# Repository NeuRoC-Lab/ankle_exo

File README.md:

# ankle_exo
This repository stores the algorithms to operate The OpenExo Styled exoskeleton.

# instructions 

To run the Arduino-Teensy CAN sender receiver test do : 

(1) Connect each of the Arduino R4 and run `pio run -e can_module_arduinos_receiver` or `pio run -e can_module_arduinos_sender` for the receiver arduino and the sender arduino respectively 

(2) Connect one Teensy, run `pio run -e can_module_teensy_receiver` / `pio run -e can_module_teensy_sender` then do same as (1) for the remaining Arduino 

## CubeMars connection with the SN65HVD230 CAN Transceiver module + Arduino Uno R4

Run the Arduino code with `pio run -e arduino_can_cubemars` which will move the motor back and forth 

# A web documentation is available at [this website](https://oscartesniere.com/ankledocs/).

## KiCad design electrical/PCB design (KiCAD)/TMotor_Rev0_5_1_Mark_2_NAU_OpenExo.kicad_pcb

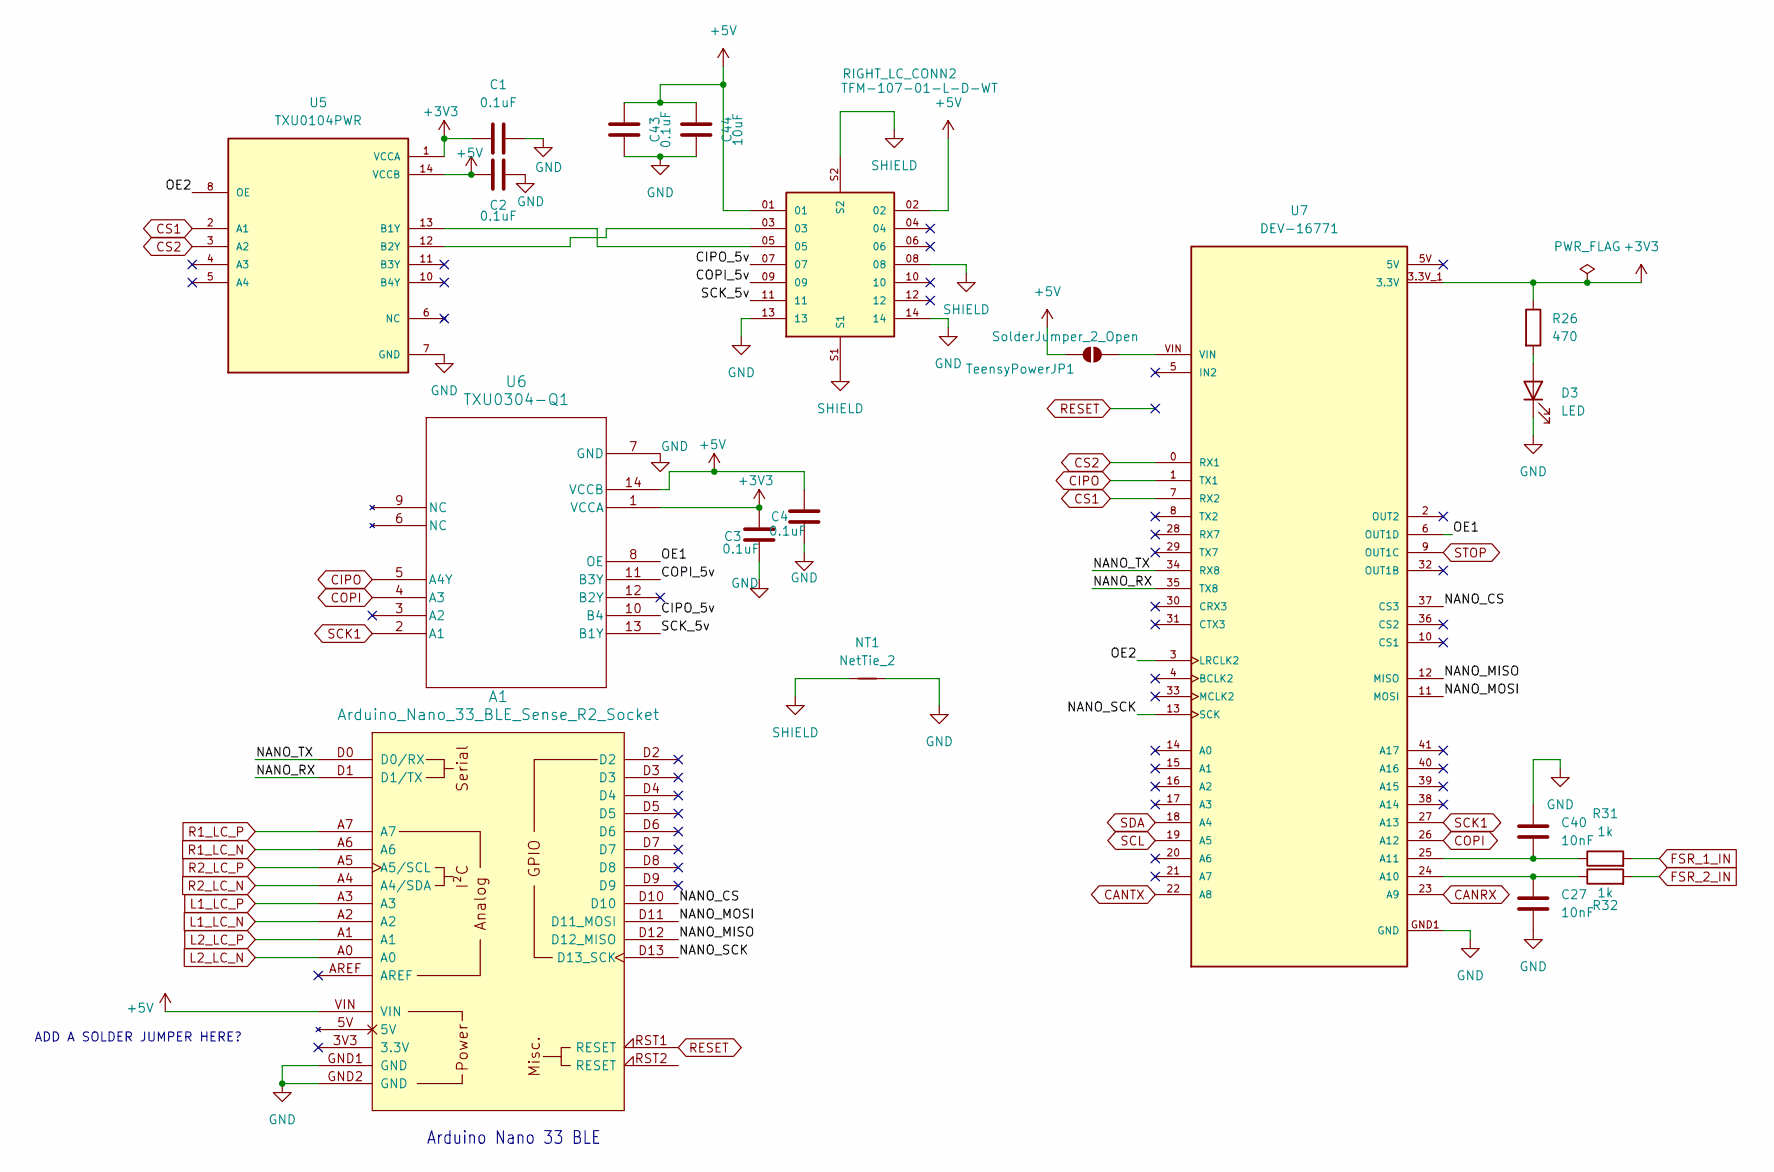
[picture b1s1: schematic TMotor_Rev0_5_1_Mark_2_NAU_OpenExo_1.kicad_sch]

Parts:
A1: Arduino_Nano_33_BLE_Sense_R2_Socket; Arduino_Nano_Every_Socket
C1, C2, C3, C4, C43: 0.1uF; C_0805_2012Metric_Pad1.18x1.45mm_HandSolder
C27, C40: 10nF; C_0805_2012Metric_Pad1.18x1.45mm_HandSolder
C44: 10uF; C_0805_2012Metric_Pad1.18x1.45mm_HandSolder
D3: LED; LED_0805_2012Metric
NT1: NetTie_2; NetTie-2_SMD_Pad0.5mm
R26: 470; R_0805_2012Metric_Pad1.20x1.40mm_HandSolder
R31, R32: 1k; R_0805_2012Metric_Pad1.20x1.40mm_HandSolder
RIGHT_LC_CONN2: TFM-107-01-L-D-WT; SAMTEC_TFM-107-01-L-D-WT; PARTREV T
TeensyPowerJP1: SolderJumper_2_Open; SolderJumper-2_P1.3mm_Open_RoundedPad1.0x1.5mm
U5: TXU0104PWR; SOIC_QPWRQ1_TEX; PARTREV A
U6: TXU0304-Q1; PW14_TXU0304-Q1_TEX
U7: DEV-16771; MODULE_DEV-16771; PARTREV 4.1

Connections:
+3V3: C1.1, C3.2, R26.1, U5.1 (VCCA), U6.1 (VCCA), U7.3.3V_1 (3.3V), U7.3.3V_2 (3.3V), U7.3.3V_3 (3.3V); also elsewhere on the board
/MCUs/CIPO_5v: RIGHT_LC_CONN2.07, U6.10 (B4)
/MCUs/COPI_5v: RIGHT_LC_CONN2.09, U6.11 (B3Y)
/MCUs/NANO_CS: A1.D10, U7.37 (CS3)
/MCUs/NANO_MISO: A1.D12 (D12_MISO), U7.12 (MISO)
/MCUs/NANO_MOSI: A1.D11 (D11_MOSI), U7.11 (MOSI)
/MCUs/NANO_RX: A1.D1 (D1/TX), U7.35 (TX8)
/MCUs/NANO_SCK: A1.D13 (D13_SCK), U7.13 (SCK)
/MCUs/NANO_TX: A1.D0 (D0/RX), U7.34 (RX8)
/MCUs/OE1: U6.8 (OE), U7.6 (OUT1D)
/MCUs/OE2: U5.8 (OE), U7.3 (LRCLK2)
/MCUs/SCK_5v: RIGHT_LC_CONN2.11, U6.13 (B1Y)
CANRX: U7.23 (A9); also elsewhere on the board
CANTX: U7.22 (A8); also elsewhere on the board
CIPO: U6.5 (A4Y), U7.1 (TX1)
COPI: U6.4 (A3), U7.26 (A12)
CS1: U5.2 (A1), U7.7 (RX2)
CS2: U5.3 (A2), U7.0 (RX1)
FSR_1_IN: R31.2; also elsewhere on the board
FSR_2_IN: R32.2; also elsewhere on the board
GND: A1.GND1 (GND), A1.GND2 (GND), C1.2, C2.2, C3.1, C4.1, C27.2, C40.1, C43.1, C44.1, D3.1 (K), NT1.2, RIGHT_LC_CONN2.13, RIGHT_LC_CONN2.14, U5.7 (GND), U6.7 (GND), U7.GND1 (GND), U7.GND2 (GND), U7.GND3 (GND), U7.GND4 (GND), U7.GND5 (GND); also elsewhere on the board
L1_LC_N: A1.A2; also elsewhere on the board
L1_LC_P: A1.A3; also elsewhere on the board
L2_LC_N: A1.A0; also elsewhere on the board
L2_LC_P: A1.A1; also elsewhere on the board
unnamed: D3.2 (A), R26.2
unnamed: TeensyPowerJP1.1 (A), U7.VIN
unnamed: RIGHT_LC_CONN2.05, U5.13 (B1Y)
unnamed: RIGHT_LC_CONN2.03, U5.12 (B2Y)
unnamed: C27.1, R32.1, U7.24 (A10)
unnamed: C40.2, R31.1, U7.25 (A11)
R1_LC_N: A1.A6; also elsewhere on the board
R1_LC_P: A1.A7; also elsewhere on the board
R2_LC_N: A1.A4 (A4/SDA); also elsewhere on the board
R2_LC_P: A1.A5 (A5/SCL); also elsewhere on the board
RESET: A1.RST1 (RESET); also elsewhere on the board
SCK1: U6.2 (A1), U7.27 (A13)
SCL: U7.19 (A5); also elsewhere on the board
SDA: U7.18 (A4); also elsewhere on the board
SHIELD: NT1.1, RIGHT_LC_CONN2.08, RIGHT_LC_CONN2.S1, RIGHT_LC_CONN2.S2; also elsewhere on the board
STOP: U7.9 (OUT1C); also elsewhere on the board

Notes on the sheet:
ADD A SOLDER JUMPER HERE?
Arduino Nano 33 BLE

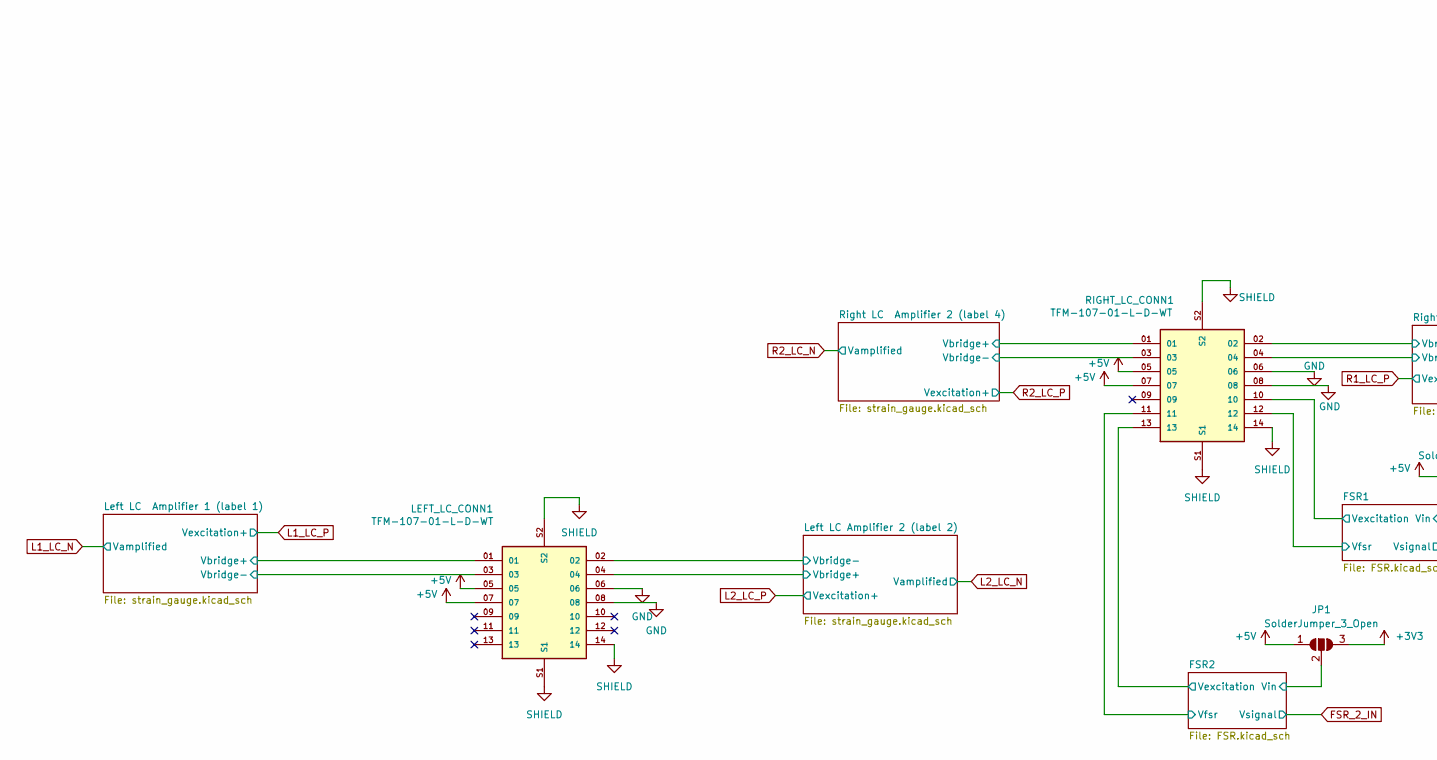
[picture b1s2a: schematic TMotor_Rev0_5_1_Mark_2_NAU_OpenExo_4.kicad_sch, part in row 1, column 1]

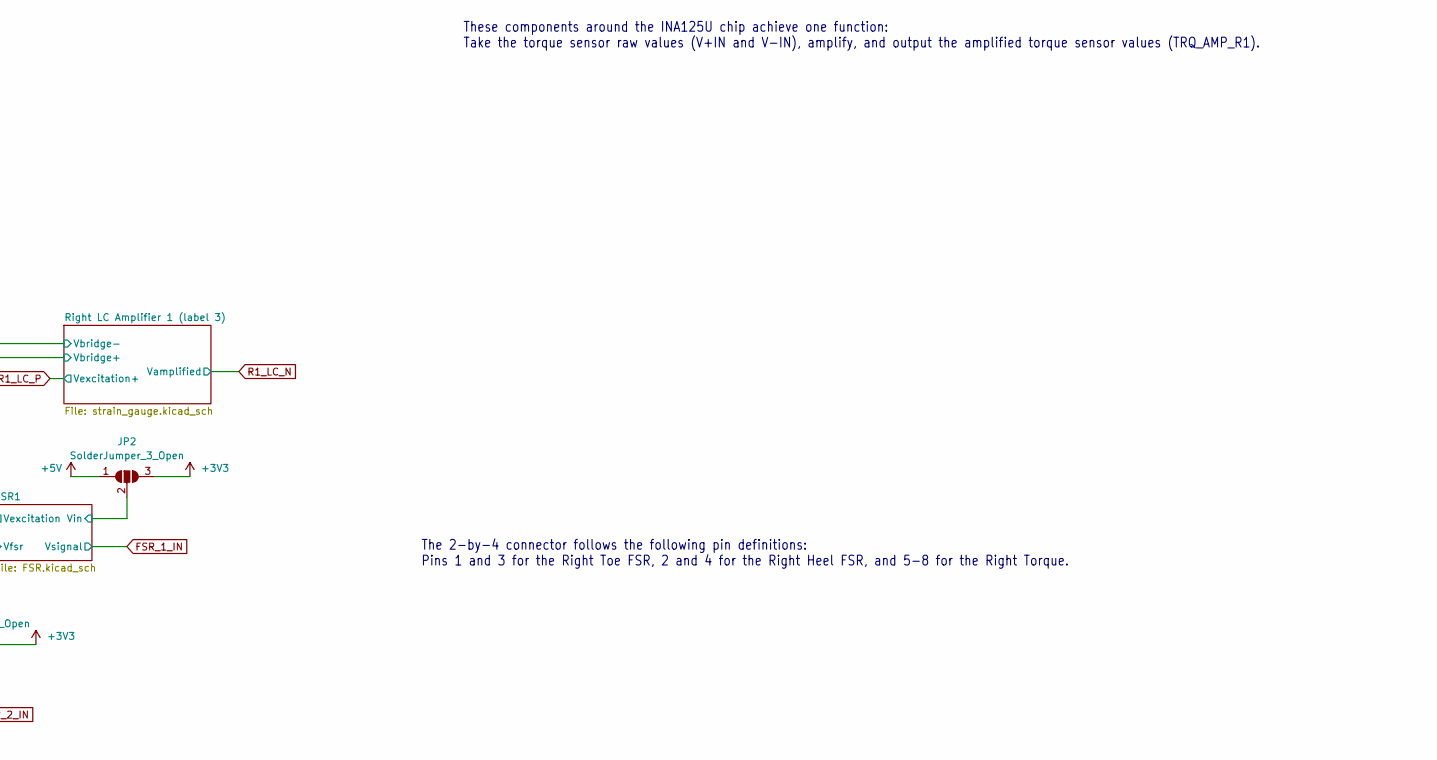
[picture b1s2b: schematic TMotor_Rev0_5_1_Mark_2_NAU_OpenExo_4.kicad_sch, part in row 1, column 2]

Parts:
JP1, JP2: SolderJumper_3_Open; SolderJumper-3_P1.3mm_Open_RoundedPad1.0x1.5mm
LEFT_LC_CONN1: TFM-107-01-L-D-WT; SAMTEC_TFM-107-01-L-D-WT; PARTREV T
RIGHT_LC_CONN1: TFM-107-01-L-D-WT; SAMTEC_TFM-107-01-L-D-WT; PARTREV T

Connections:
+3V3: JP1.3 (B), JP2.3 (B); also elsewhere on the board
/Load cells/FSR1/Vexcitation: JP2.2 (C), RIGHT_LC_CONN1.10
/Load cells/FSR2/Vexcitation: JP1.2 (C), RIGHT_LC_CONN1.13
/Load cells/Left LC Amplifier 1 (label 1)/Vbridge+: LEFT_LC_CONN1.01; also elsewhere on the board
/Load cells/Left LC Amplifier 1 (label 1)/Vbridge-: LEFT_LC_CONN1.03; also elsewhere on the board
/Load cells/Left LC Amplifier 2 (label 2)/Vbridge+: LEFT_LC_CONN1.04; also elsewhere on the board
/Load cells/Left LC Amplifier 2 (label 2)/Vbridge-: LEFT_LC_CONN1.02; also elsewhere on the board
/Load cells/Right LC Amplifier 2 (label 4)/Vbridge+: RIGHT_LC_CONN1.01; also elsewhere on the board
/Load cells/Right LC Amplifier 2 (label 4)/Vbridge-: RIGHT_LC_CONN1.03; also elsewhere on the board
/Load cells/Right LC Amplifier 1 (label 3)/Vbridge+: RIGHT_LC_CONN1.04; also elsewhere on the board
/Load cells/Right LC Amplifier 1 (label 3)/Vbridge-: RIGHT_LC_CONN1.02; also elsewhere on the board
FSR_1_IN: RIGHT_LC_CONN1.12; also elsewhere on the board
FSR_2_IN: RIGHT_LC_CONN1.11; also elsewhere on the board
GND: LEFT_LC_CONN1.06, LEFT_LC_CONN1.08, RIGHT_LC_CONN1.06, RIGHT_LC_CONN1.08; also elsewhere on the board
SHIELD: LEFT_LC_CONN1.14, LEFT_LC_CONN1.S1, LEFT_LC_CONN1.S2, RIGHT_LC_CONN1.14, RIGHT_LC_CONN1.S1, RIGHT_LC_CONN1.S2; also elsewhere on the board

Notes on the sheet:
The 2-by-4 connector follows the following pin definitions: Pins 1 and 3 for the Right Toe FSR, 2 and 4 for the Right Heel FSR, and 5-8 for the Right Torque.
These components around the INA125U chip achieve one function: Take the torque sensor raw values (V+IN and V-IN), amplify, and output the amplified torque sensor values (TRQ_AMP_R1).

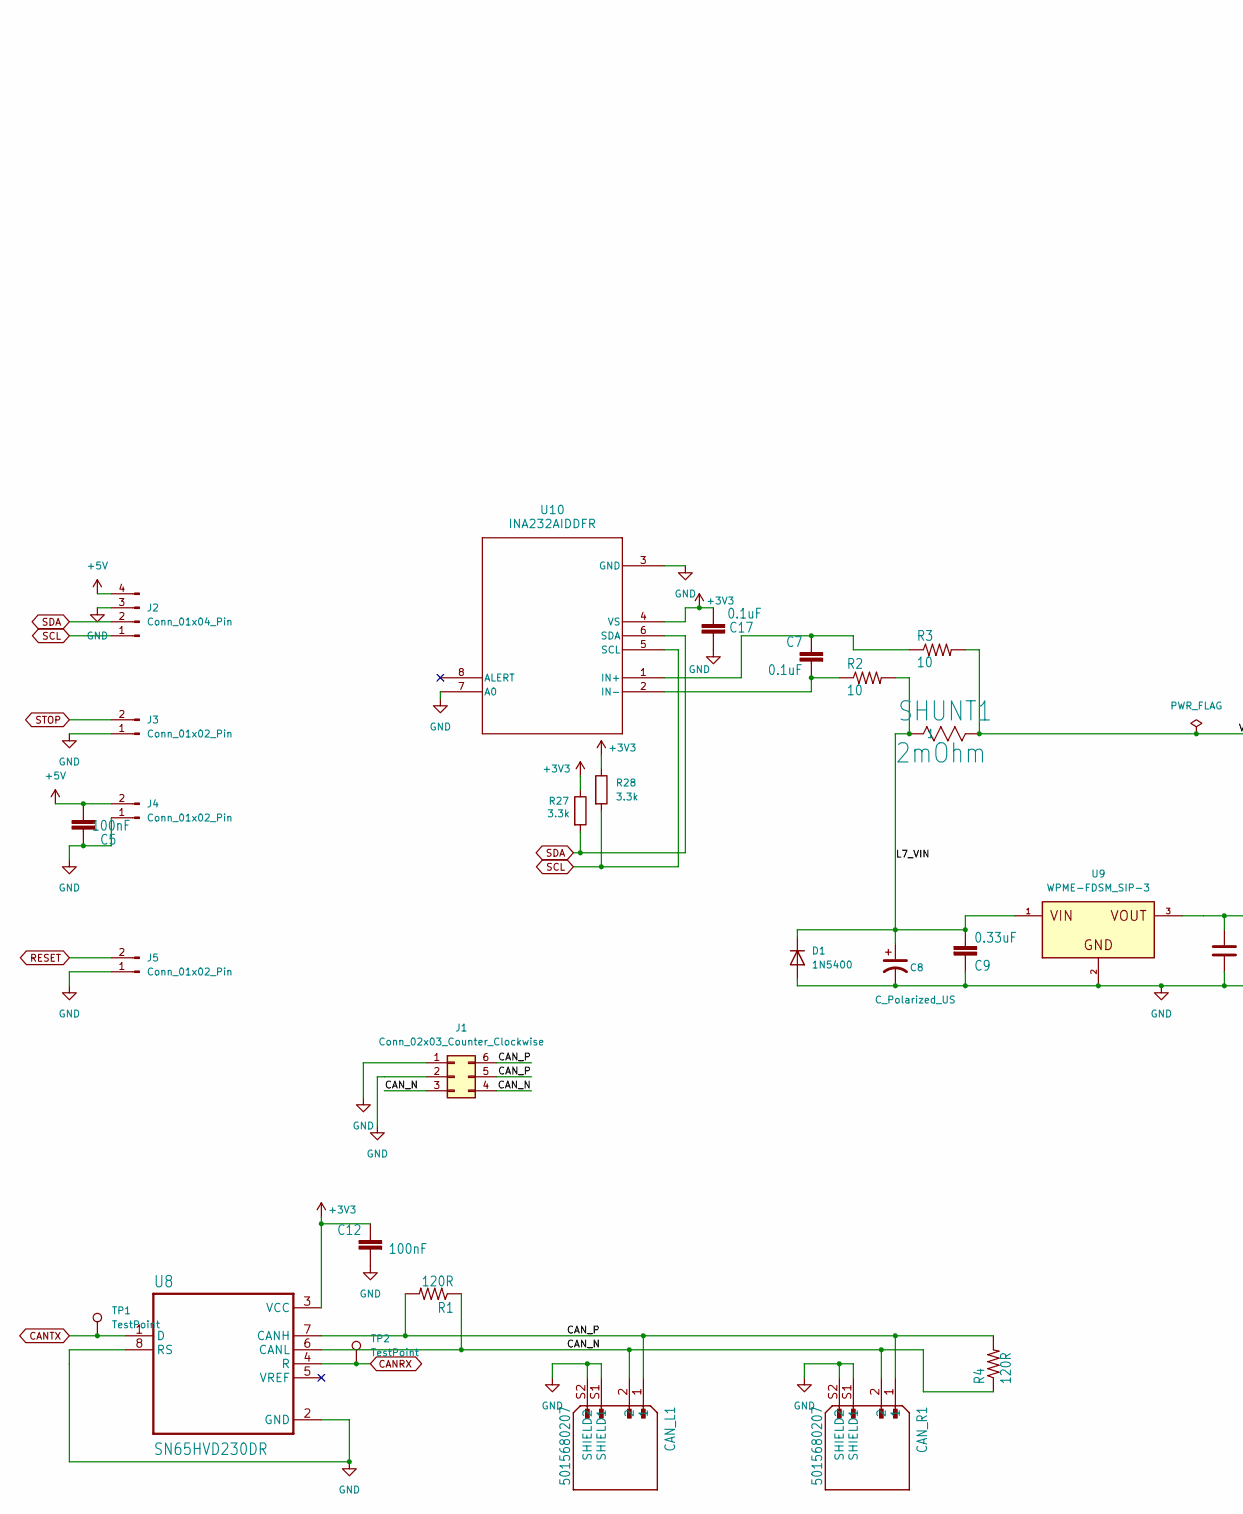
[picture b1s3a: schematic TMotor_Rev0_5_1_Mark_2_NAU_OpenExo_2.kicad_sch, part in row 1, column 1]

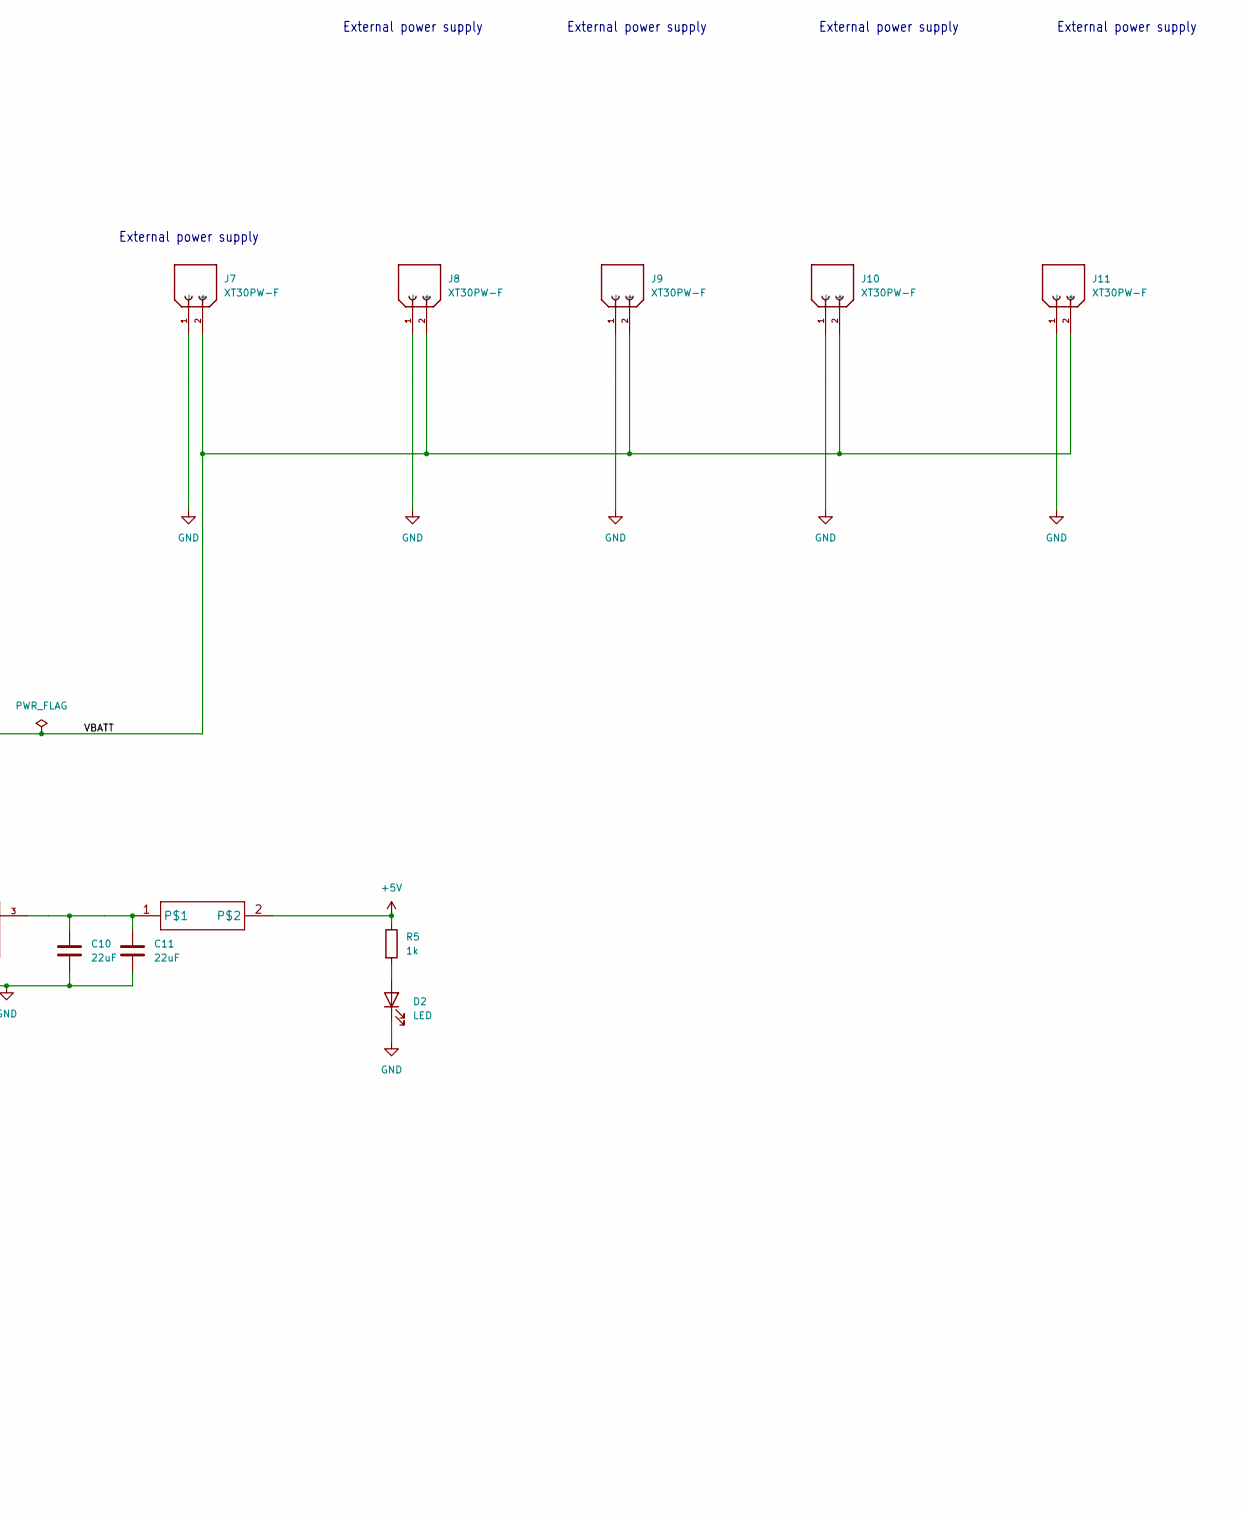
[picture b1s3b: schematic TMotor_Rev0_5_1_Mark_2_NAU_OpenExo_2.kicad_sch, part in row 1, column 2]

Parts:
C5, C12: 100nF; C_0805_2012Metric_Pad1.18x1.45mm_HandSolder
C7, C17: 0.1uF; C_0805_2012Metric_Pad1.18x1.45mm_HandSolder
C8: C_Polarized_US; CP_Radial_D10.0mm_P5.00mm
C9: 0.33uF; C_0805_2012Metric_Pad1.18x1.45mm_HandSolder
C10, C11: 22uF; C_0805_2012Metric_Pad1.18x1.45mm_HandSolder
CAN_L1: 5015680207; MOLEX_5015680207
CAN_R1: 5015680207; MOLEX_5015680207
D1: 1N5400; D_DO-201AD_P15.24mm_Horizontal
D2: LED; LED_0805_2012Metric
J1: Conn_02x03_Counter_Clockwise; PinHeader_2x03_P2.54mm_Vertical
J2: Conn_01x04_Pin; PinHeader_1x04_P2.54mm_Vertical
J3, J4, J5: Conn_01x02_Pin; PinHeader_1x02_P2.54mm_Vertical
J7, J8, J9, J10, J11: XT30PW-F; AMASS_XT30U-F_1x02_P5.0mm_Vertical; PARTREV 1.2
R1, R4: 120R; R_0805_2012Metric_Pad1.20x1.40mm_HandSolder
R2, R3: 10; R_0805_2012Metric_Pad1.20x1.40mm_HandSolder
R5: 1k; R_0805_2012Metric_Pad1.20x1.40mm_HandSolder
R27, R28: 3.3k; R_0805_2012Metric_Pad1.20x1.40mm_HandSolder
SHUNT1: 2mOhm; STA_CSNL2512(2)_STP
TP1, TP2: TestPoint; TestPoint_Keystone_5000-5004_Miniature
U8: SN65HVD230DR; SOIC127P599X175-8N
U9: WPME-FDSM_SIP-3; WPME-FDSM_17301XX35; DigiKey_Part_Number 732-173010535-ND
U10: INA232AIDDFR; SOT_32AIDDFR_TEX
U$1: 0458002.DR; FUSE_LITTEL_448

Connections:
+3V3: C12.1, C17.2, R27.1, R28.1, U8.3 (VCC), U10.4 (VS); also elsewhere on the board
/CAN and peripherals./CAN_N: CAN_L1.2, CAN_R1.2, J1.3, J1.4, R1.1, R4.1, U8.6 (CANL)
/CAN and peripherals./CAN_P: CAN_L1.1, CAN_R1.1, J1.5, J1.6, R1.2, R4.2, U8.7 (CANH)
/CAN and peripherals./L7_VIN: C8.1, C9.2, D1.1 (K), R2.2, SHUNT1.1, U9.1
/CAN and peripherals./VBATT: J7.2 (+), J8.2 (+), J9.2 (+), J10.2 (+), J11.2 (+), R3.2, SHUNT1.2
CANRX: TP2.1, U8.4 (R); also elsewhere on the board
CANTX: TP1.1, U8.1 (D); also elsewhere on the board
GND: C5.1, C8.2, C9.1, C10.2, C11.2, C12.2, C17.1, CAN_L1.S1 (SHIELD1), CAN_L1.S2 (SHIELD2), CAN_R1.S1 (SHIELD1), CAN_R1.S2 (SHIELD2), D1.2 (A), D2.1 (K), J1.1, J1.2, J2.3, J3.1, J4.1, J5.1, J7.1 (-), J8.1 (-), J9.1 (-), J10.1 (-), J11.1 (-), U8.2 (GND), U8.8 (RS), U9.2, U10.3 (GND), U10.7 (A0); also elsewhere on the board
unnamed: D2.2 (A), R5.2
unnamed: C7.1, R3.1, U10.1 (IN+)
unnamed: C7.2, R2.1, U10.2 (IN-)
unnamed: C10.1, C11.1, U9.3, U$1.1
RESET: J5.2; also elsewhere on the board
SCL: J2.1, R28.2, U10.5 (SCL); also elsewhere on the board
SDA: J2.2, R27.2, U10.6 (SDA); also elsewhere on the board
STOP: J3.2; also elsewhere on the board

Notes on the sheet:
External power supply

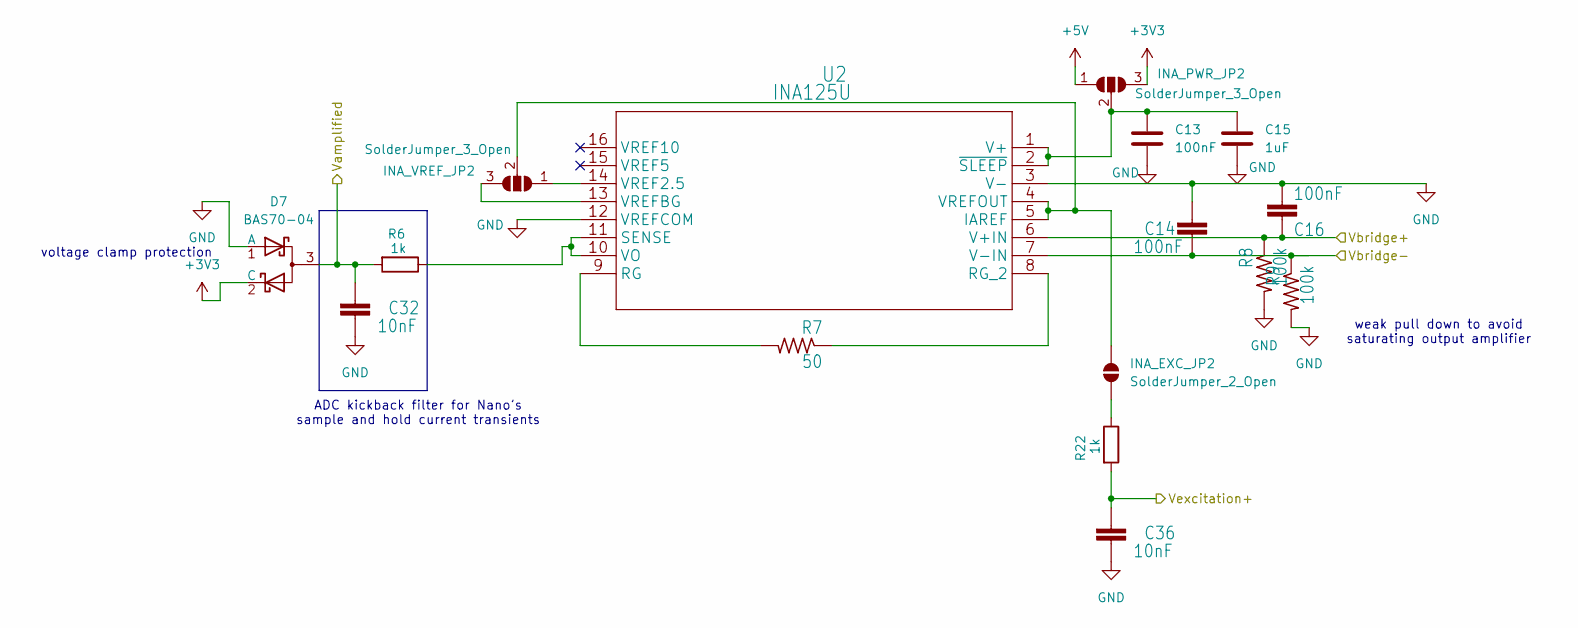
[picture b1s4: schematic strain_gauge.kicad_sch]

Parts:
C13, C14, C16: 100nF; C_0805_2012Metric_Pad1.18x1.45mm_HandSolder
C15: 1uF; C_0805_2012Metric_Pad1.18x1.45mm_HandSolder
C32, C36: 10nF; C_0805_2012Metric_Pad1.18x1.45mm_HandSolder
D7: BAS70-04; P200_SOT-23
INA_EXC_JP2: SolderJumper_2_Open; SolderJumper-2_P1.3mm_Open_RoundedPad1.0x1.5mm
INA_PWR_JP2: SolderJumper_3_Open; SolderJumper-3_P1.3mm_Open_RoundedPad1.0x1.5mm_NumberLabels
INA_VREF_JP2: SolderJumper_3_Open; SolderJumper-3_P1.3mm_Open_RoundedPad1.0x1.5mm_NumberLabels
R6, R22: 1k; R_0805_2012Metric_Pad1.20x1.40mm_HandSolder
R7: 50; R_0805_2012Metric_Pad1.20x1.40mm_HandSolder
R8, R9: 100k; R_0805_2012Metric_Pad1.20x1.40mm_HandSolder
U2: INA125U; D16

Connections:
+3V3: D7.2 (C), INA_PWR_JP2.3 (B); also elsewhere on the board
/Load cells/Left LC Amplifier 2 (label 2)/Vbridge+: C16.1, R8.1, U2.6 (V+IN); also elsewhere on the board
/Load cells/Left LC Amplifier 2 (label 2)/Vbridge-: C14.1, R9.1, U2.7 (V-IN); also elsewhere on the board
GND: C13.2, C14.2, C15.2, C16.2, C32.1, C36.1, D7.1 (A), R8.2, R9.2, U2.3 (V-), U2.12 (VREFCOM); also elsewhere on the board
L2_LC_N: C32.2, D7.3, R6.2; also elsewhere on the board
L2_LC_P: C36.2, R22.2; also elsewhere on the board
unnamed: INA_EXC_JP2.2 (B), R22.1
unnamed 48: INA_VREF_JP2.3 (B), U2.13 (VREFBG); also elsewhere on the board
unnamed: R7.2, U2.9 (RG)
unnamed: R7.1, U2.8 (RG_2)
unnamed: R6.1, U2.10 (VO), U2.11 (SENSE)

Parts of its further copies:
C18, C19, C21, C23, C24, C26, C28, C29, C31: 100nF; C_0805_2012Metric_Pad1.18x1.45mm_HandSolder
C20, C25, C30: 1uF; C_0805_2012Metric_Pad1.18x1.45mm_HandSolder
C33, C34, C35, C37, C38, C39: 10nF; C_0805_2012Metric_Pad1.18x1.45mm_HandSolder
D8, D9, D10: BAS70-04; P200_SOT-23
INA_EXC_JP1, INA_EXC_JP3, INA_EXC_JP4: SolderJumper_2_Open; SolderJumper-2_P1.3mm_Open_RoundedPad1.0x1.5mm
R10, R14, R18, R23, R24, R25: 1k; R_0805_2012Metric_Pad1.20x1.40mm_HandSolder
R11, R15, R19: 50; R_0805_2012Metric_Pad1.20x1.40mm_HandSolder
R12, R13, R16, R17, R20, R21: 100k; R_0805_2012Metric_Pad1.20x1.40mm_HandSolder
U1, U3, U4: INA125U; D16

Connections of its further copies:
+3V3: D8.2 (C), D9.2 (C), D10.2 (C); also elsewhere on the board
/Load cells/Left LC Amplifier 1 (label 1)/Vbridge+: C21.1, R12.1, U1.6 (V+IN); also elsewhere on the board
/Load cells/Left LC Amplifier 1 (label 1)/Vbridge-: C19.1, R13.1, U1.7 (V-IN); also elsewhere on the board
/Load cells/Right LC Amplifier 2 (label 4)/Vbridge+: C26.1, R16.1, U4.6 (V+IN); also elsewhere on the board
/Load cells/Right LC Amplifier 2 (label 4)/Vbridge-: C24.1, R17.1, U4.7 (V-IN); also elsewhere on the board
/Load cells/Right LC Amplifier 1 (label 3)/Vbridge+: C31.1, R20.1, U3.6 (V+IN); also elsewhere on the board
/Load cells/Right LC Amplifier 1 (label 3)/Vbridge-: C29.1, R21.1, U3.7 (V-IN); also elsewhere on the board
GND: C18.2, C19.2, C20.2, C21.2, C23.2, C24.2, C25.2, C26.2, C28.2, C29.2, C30.2, C31.2, C33.1, C34.1, C35.1, C37.1, C38.1, C39.1, D8.1 (A), D9.1 (A), D10.1 (A), R12.2, R13.2, R16.2, R17.2, R20.2, R21.2, U1.3 (V-), U1.12 (VREFCOM), U3.3 (V-), U3.12 (VREFCOM), U4.3 (V-), U4.12 (VREFCOM); also elsewhere on the board
L1_LC_N: C33.2, D8.3, R10.2; also elsewhere on the board
L1_LC_P: C37.2, R23.2; also elsewhere on the board
unnamed: INA_EXC_JP1.1 (A), U1.4 (VREFOUT), U1.5 (IAREF), U1.14 (VREF2.5)
unnamed: INA_EXC_JP1.2 (B), R23.1
unnamed: INA_EXC_JP3.1 (A), U3.4 (VREFOUT), U3.5 (IAREF), U3.14 (VREF2.5)
unnamed: INA_EXC_JP3.2 (B), R25.1
unnamed: INA_EXC_JP4.1 (A), U4.4 (VREFOUT), U4.5 (IAREF), U4.14 (VREF2.5)
unnamed: INA_EXC_JP4.2 (B), R24.1
unnamed 48: U1.13 (VREFBG), U3.13 (VREFBG), U4.13 (VREFBG); also elsewhere on the board
unnamed: R11.2, U1.9 (RG)
unnamed: R11.1, U1.8 (RG_2)
unnamed: R10.1, U1.10 (VO), U1.11 (SENSE)
unnamed: R19.2, U3.9 (RG)
unnamed: R19.1, U3.8 (RG_2)
unnamed: R18.1, U3.10 (VO), U3.11 (SENSE)
unnamed: R15.2, U4.9 (RG)
unnamed: R15.1, U4.8 (RG_2)
unnamed: R14.1, U4.10 (VO), U4.11 (SENSE)
R1_LC_N: C35.2, D10.3, R18.2; also elsewhere on the board
R1_LC_P: C39.2, R25.2; also elsewhere on the board
R2_LC_N: C34.2, D9.3, R14.2; also elsewhere on the board
R2_LC_P: C38.2, R24.2; also elsewhere on the board

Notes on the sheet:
voltage clamp protection
weak pull down to avoid saturating output amplifier
ADC kickback filter for Nano's sample and hold current transients

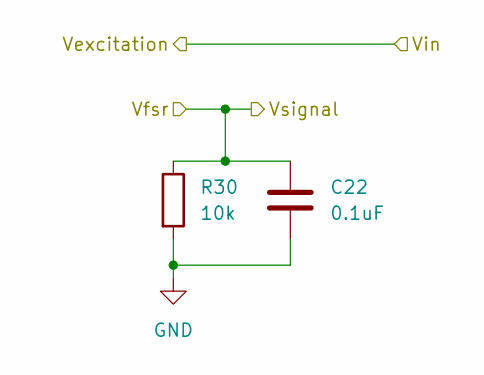
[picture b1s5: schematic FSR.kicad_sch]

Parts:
C22: 0.1uF; C_0805_2012Metric_Pad1.18x1.45mm_HandSolder
R30: 10k; R_0805_2012Metric_Pad1.20x1.40mm_HandSolder

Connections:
FSR_1_IN: C22.1, R30.1; also elsewhere on the board
GND: C22.2, R30.2; also elsewhere on the board

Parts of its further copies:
C6: 0.1uF; C_0805_2012Metric_Pad1.18x1.45mm_HandSolder
R29: 10k; R_0805_2012Metric_Pad1.20x1.40mm_HandSolder

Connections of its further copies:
FSR_2_IN: C6.1, R29.1; also elsewhere on the board
GND: C6.2, R29.2; also elsewhere on the board

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
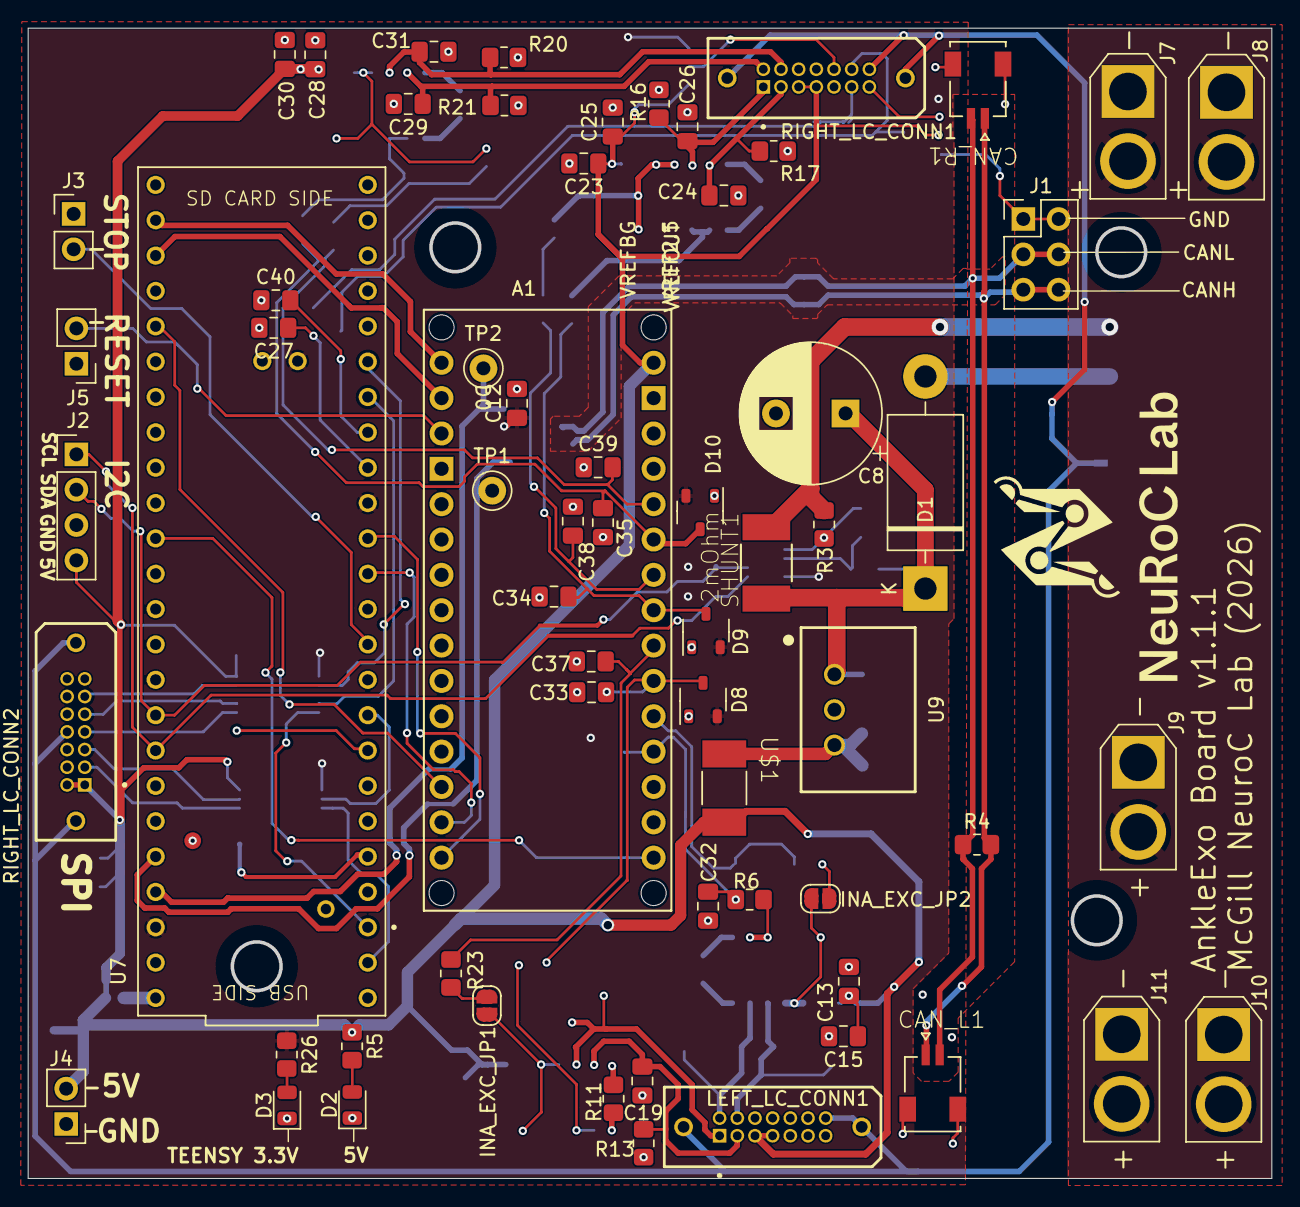
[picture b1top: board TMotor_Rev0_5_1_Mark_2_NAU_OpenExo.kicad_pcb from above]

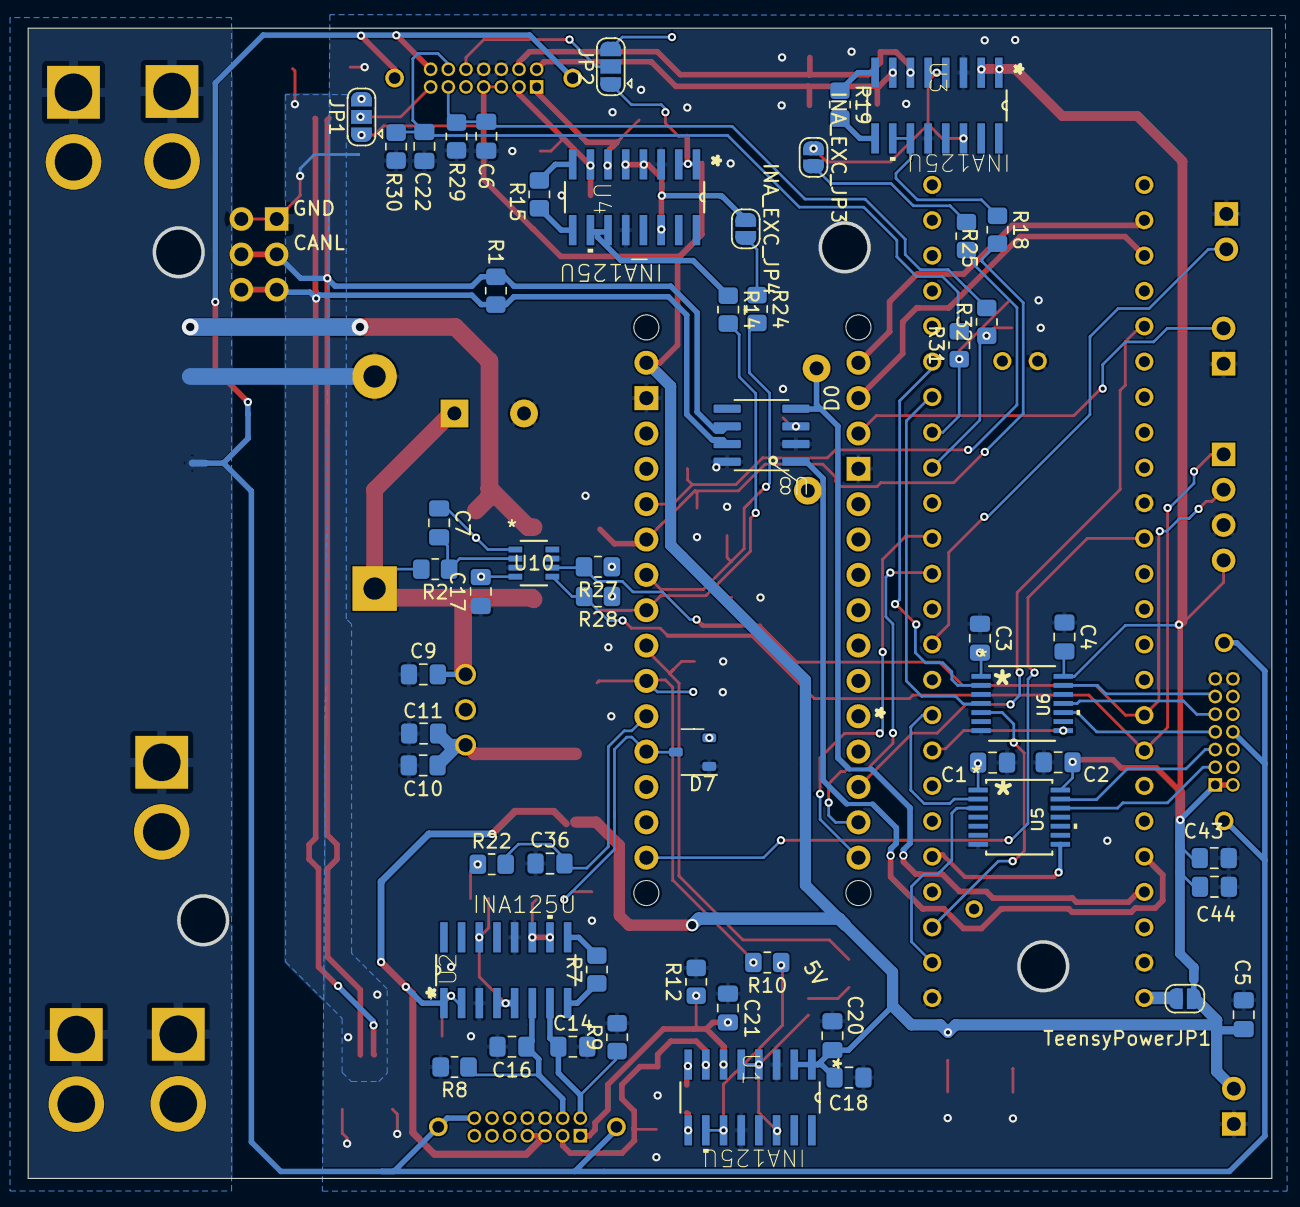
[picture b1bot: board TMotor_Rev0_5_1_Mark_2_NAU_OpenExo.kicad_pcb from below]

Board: 2 copper layers, 89.2 x 82.4 mm, 119 parts (55 on the bottom side), 80 nets.

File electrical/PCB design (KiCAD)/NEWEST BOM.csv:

"Id";"Designator";"Footprint";"Quantity";"Designation";"Supplier and ref";
1;"U7";"MODULE_DEV-16771";1;"DEV-16771";;;
2;"C24,C26,C29,C19,C23,C28,C13,C31,C21,C7,C6,C16,C18,C5,C14";"C_0805_2012Metric_Pad1.18x1.45mm_HandSolder";15;"100nF";;;
3;"C38,C37,C33,C34,C32,C35,C39,C36";"C_0805_2012Metric_Pad1.18x1.45mm_HandSolder";8;"10nF";;;
4;"RIGHT_LC_CONN1,LEFT_LC_CONN1,RIGHT_LC_CONN2";"SAMTEC_TFM-107-01-L-D-WT";3;"TFM-107-01-L-D-WT";;;
5;"CAN_L1,CAN_R1";"MOLEX_5015680207";2;"5015680207";;;
6;"D1";"D_DO-201AD_P15.24mm_Horizontal";1;"1N5400";;;
7;"R4,R1";"R_0805_2012Metric_Pad1.20x1.40mm_HandSolder";2;"120R";;;
8;"R21,R16,R13,R17,R20,R8,R9,R12";"R_0805_2012Metric_Pad1.20x1.40mm_HandSolder";8;"100k";;;
9;"C8";"CP_Radial_D10.0mm_P5.00mm";1;"C_Polarized_US";;;
10;"J4,J3,J5";"PinHeader_1x02_P2.54mm_Vertical";3;"Conn_01x02_Pin";;;
11;"A1";"Arduino_Nano_Every_Socket";1;"Arduino_Nano_33_BLE_Sense_R2_Socket";;;
12;"J2";"PinHeader_1x04_P2.54mm_Vertical";1;"Conn_01x04_Pin";;;
13;"D10,D8,D9,D7";"P200_SOT-23";4;"BAS70-04";;;
14;"SHUNT1";"STA_CSNL2512(2)_STP";1;"2mOhm";;;
15;"TP2,TP1";"TestPoint_Keystone_5000-5004_Miniature";2;"TestPoint";;;
16;"U9";"WPME-FDSM_17301XX35";1;"WPME-FDSM_SIP-3";;;
17;"R23,R6,R14,R18,R10,R25,R22,R24";"R_0805_2012Metric_Pad1.20x1.40mm_HandSolder";8;"1k";;;
18;"J9,J11,J10,J8,J7";"AMASS_XT30U-F_1x02_P5.0mm_Vertical";5;"XT30PW-F";;;
19;"J6";"PinHeader_1x03_P2.54mm_Vertical";1;"Conn_01x03_Pin";;;
20;"C15,C25,C30,C20";"C_0805_2012Metric_Pad1.18x1.45mm_HandSolder";4;"1uF";;;
21;"D2";"LED_0805_2012Metric";1;"LED";;;
22;"R5";"R_0805_2012Metric_Pad1.20x1.40mm_HandSolder";1;"600kR";;;
23;"U$1";"FUSE_LITTEL_448";1;"0458002.DR";;;
24;"R3";"R_0805_2012Metric_Pad1.20x1.40mm_HandSolder";1;"10";;;
25;"R11,R15,R7,R19";"R_0805_2012Metric_Pad1.20x1.40mm_HandSolder";4;"50";;;
26;"C10,C11";"C_0805_2012Metric_Pad1.18x1.45mm_HandSolder";2;"22uF";;;
27;"U2,U4,U1,U3";"D16";4;"INA125U";;;
28;"R2";"R_0805_2012Metric_Pad1.20x1.40mm_HandSolder";1;"10R";;;
29;"C4,C2,C1,C3";"C_0805_2012Metric_Pad1.18x1.45mm_HandSolder";4;"0.1uF";;;
30;"U5";"SOIC_QPWRQ1_TEX";1;"TXU0104PWR";;;
31;"C9";"C_0805_2012Metric_Pad1.18x1.45mm_HandSolder";1;"0.33uF";;;
32;"U8";"SOIC127P599X175-8N";1;"SN65HVD230DR";;;
33;"U6";"PW14_TXU0304-Q1_TEX";1;"TXU0304-Q1";;;
34;"INA1";"D8_TEX";1;"~";;;

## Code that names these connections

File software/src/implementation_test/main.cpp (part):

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constexpr int CS_RIGHT = 9;

// SPI pins : using SPI1 port (do a test before with the Arduino slave / Teensy Master code)
constexpr int SCK1 = 27;
constexpr int MOSI1 = 26;
constexpr int MISO1 = 1;

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bool encoders = false;

// CAN :
// CANRX = 23
// CANTX = 22
FlexCAN_T4<CAN1, RX_SIZE_256, TX_SIZE_16> CANbus;

String serialLine;
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
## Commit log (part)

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2026-06-15 Migrated project files to new
2026-06-15 instructions
2026-06-22 Add hi file to ankledocs directory
2026-06-22 Updated AnkleDocs Documentation on the Mechanical Side
2026-06-22 Fix formatting of serial print statements
2026-06-22 Finish MIT Mode Motor Plotting Code (not tested yet)
2026-06-23 Fix formatting and improve data handling in plotMotorMIT.py
2026-06-23 OOped the different components ; Moved KiCAD project to Github ; refactored website
2026-06-23 refactored code
    I moved your python code to `src` @siqii147 . All the otehr test files have been moved to a `test` folder
2026-06-24 fixed issues
2026-06-24 Updated Motor Testing Code (works)
2026-06-24 fixes
2026-06-24 Servo Mode Python Plotting Code Done
2026-06-25 fixed Servo mode class
2026-06-26 26/06 schematics updates
    see the changelog on the documentation /electrical/pcb
2026-06-28 Updated KiCAD for next iteration (some minor fixes) ; functional Servo controller and MIT is working over serial
2026-06-28 refactored CANMotor interfaces
2026-06-29 Modularization of plotting scripts
    Started refactoring plotting scripts to be modular by defining classes for main actions.
2026-06-29 Finish script for both encoders
2026-06-29 Modified Encoders_unified.cpp to compute ankle velocity using EWMA
2026-06-29 Update velocity logging to include filtered values
